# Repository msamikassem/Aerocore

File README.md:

# Aerocore — 3" Flight Controller

Aerocore is a flight controller for 3-inch FPV drones, built around an STM32F411 microcontroller and a BMI270 IMU. It handles IMU sensing, ESC motor control, USB configuration, and power regulation from a 4S LiPo on a single 4-layer board.

## What it does

- Runs an STM32F411CEU6 (Cortex-M4, 100MHz) as the main flight computer
- BMI270 6-axis IMU over SPI for gyro/accel
- USB-C mainly for serial communication with a PC
- Powers itself from a 4S LiPo, steps down to 5V (buck) and 3.3V (LDO) on board
- Drives 4 ESCs via PWM 
- UART header for an ELRS receiver
- Dedicated ST-Link header for programming/debugging
- 2 status LEDs + 2 power LEDS (5v and 3v)

## Key specs

| | |
|---|---|
| MCU | STM32F411CEU6, 100MHz Cortex-M4, QFN48 |
| IMU | Bosch BMI270, SPI |
| Input power | 4S LiPo (up to 60A absolute max draw, 15A per motor) |
| Onboard rails | 5V (LMR51430 buck), 3.3V (TLV75533 LDO) |
| USB | USB-C, USB2.0 full-speed |
| Board | 4 layers, 36×36mm, 1.6mm thick |
| Stackup | JLC04161H-7628 (1oz outer / 0.5oz inner copper) |
| Mounting holes | 4× M2.5, 26.5×26.5mm spacing|

## Repo layout

```
hardware/                           -> PCB files
    kicad/                          -> the actual schematic + PCB source files (final version)
    Component/      
        Data_sheets/                -> Data sheets of chosen components 
        My_FootPrints.pretty/       -> FootPrints not avaliable on KiCAD
        Schematics/                 -> Schematics not avaliable on KiCAD
        3D part/                    -> Components' 3D model
    archive/                        -> PCB V1
    manufacturing/                  -> files needed by PCB manufacturer
        bom/                        -> bill of material
        cpl/                        -> component placement
        DRC/                        -> KiCAD Error and warning reports
    
firmware/                           -> flight firmware
docs/
    design-log                      -> PCB design decisions and difficulties
    specs                           -> PCB specifications  
```

## Status

- [X] Schematic design
- [X] PCB layout
- [X] Ordered from JLCPCB
- [X] Board assembled and bring-up tested
- [ ] Firmware
- [ ] First flight

## Tools used

- KiCad 7 for schematic + PCB

## License

MIT — see [LICENSE](LICENSE). Feel free to use any of this for your own projects; if you spot a mistake I haven't caught yet, I'd genuinely like to know.

## Author

Mohammed Kassem — built as a personal project. [msamikassem@gmail.com/ linkedin.com/in/msamikassem]

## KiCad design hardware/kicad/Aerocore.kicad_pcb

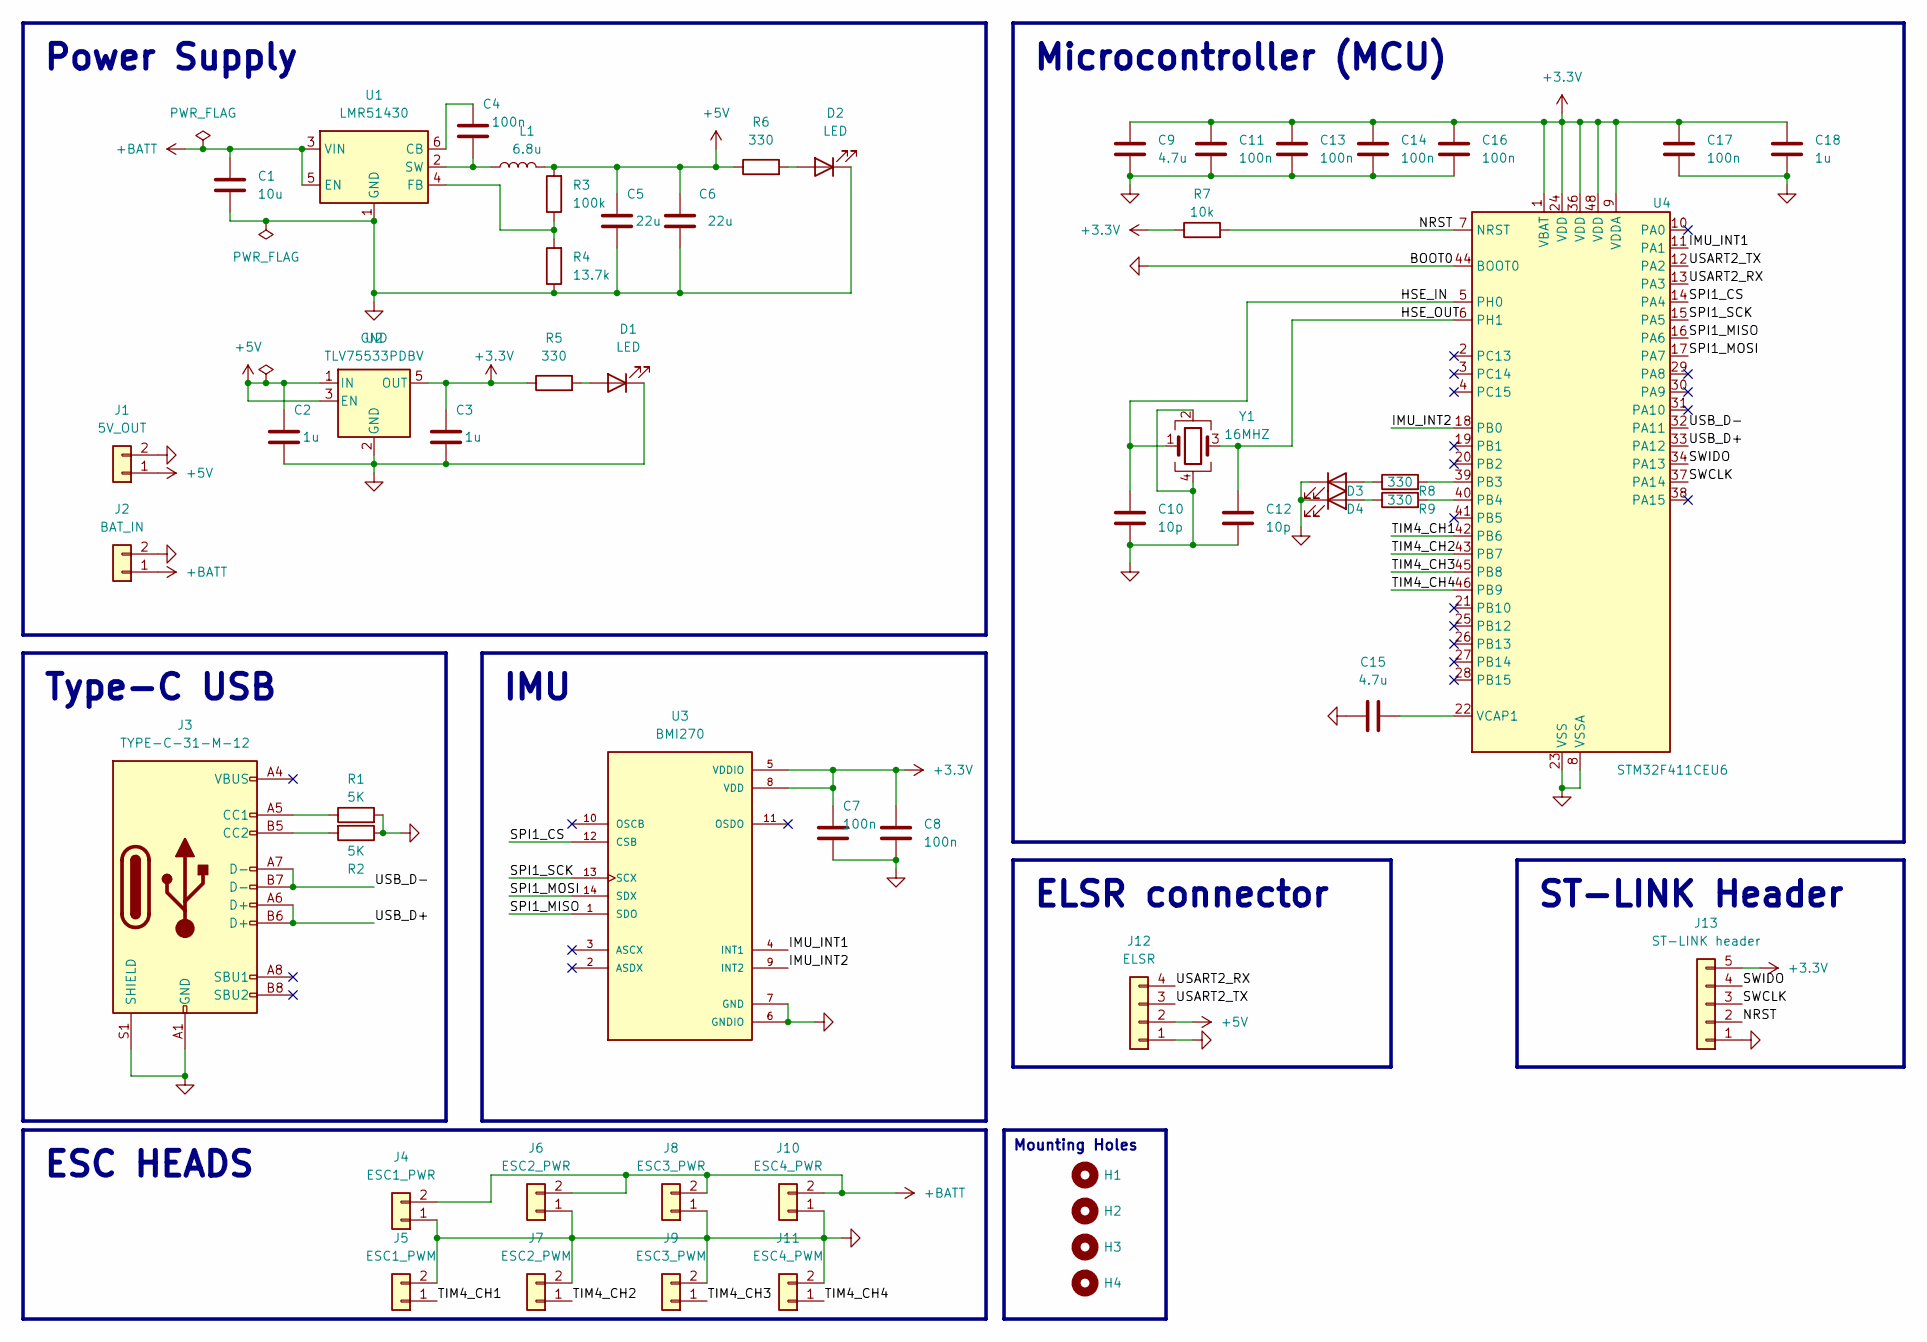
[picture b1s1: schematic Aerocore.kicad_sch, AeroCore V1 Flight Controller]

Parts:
C1: 10u; C_0603_1608Metric
C2, C3, C18: 1u; C_0603_1608Metric
C4, C7, C8, C11, C13, C14, C16, C17: 100n; C_0402_1005Metric
C5, C6: 22u; C_1206_3216Metric
C9, C15: 4.7u; C_0603_1608Metric
C10, C12: 10p; C_0603_1608Metric
D1, D2, D3, D4: LED; LED_0603_1608Metric
H1, H2, H3, H4: MountingHole_2.7mm
J1: 5V_OUT; Power_Pad_1.5x1.5mm
J2: BAT_IN; Power_Pad_1.5x1.5mm
J3: TYPE-C-31-M-12; USB_C_Receptacle_G-Switch_GT-USB-7010ASV
J4: ESC1_PWR; Power_Pad_2.5x3.5mm
J5: ESC1_PWM; Power_Pad_1.5x1.5mm
J6: ESC2_PWR; Power_Pad_2.5x3.5mm
J7: ESC2_PWM; Power_Pad_1.5x1.5mm
J8: ESC3_PWR; Power_Pad_2.5x3.5mm
J9: ESC3_PWM; Power_Pad_1.5x1.5mm
J10: ESC4_PWR; Power_Pad_2.5x3.5mm
J11: ESC4_PWM; Power_Pad_1.5x1.5mm
J12: ELSR; Power_Pad_4_1.5x1.5mm
J13: ST-LINK header; Solder_Pad_5_1.5x1.5mm
L1: 6.8u; L_Sunlord_MWSA0603S
R1, R2: 5K; R_0603_1608Metric
R3: 100k; R_0603_1608Metric
R4: 13.7k; R_0603_1608Metric
R5, R6, R8, R9: 330; R_0603_1608Metric
R7: 10k; R_0603_1608Metric
U1: LMR51430; SOT-23-6
U2: TLV75533PDBV; SOT-23-5
U3: BMI270; XDCR_BMI270
U4: STM32F411CEU6; QFN-48-1EP_7x7mm_P0.5mm_EP5.6x5.6mm
Y1: 16MHZ; Crystal_SMD_3225-4Pin_3.2x2.5mm

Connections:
+3.3V: C3.1, C7.1, C8.1, C9.1, C11.1, C13.1, C14.1, C16.1, C17.1, C18.1, J13.5, R5.1, R7.1, U2.5 (OUT), U3.5 (VDDIO), U3.8 (VDD), U4.1 (VBAT), U4.9 (VDDA), U4.24 (VDD), U4.36 (VDD), U4.48 (VDD)
+5V: C2.1, C5.1, C6.1, J1.1, J12.2, L1.2, R3.2, R6.1, U2.1 (IN), U2.3 (EN)
+BATT: C1.1, J2.1, J4.2, J6.2, J8.2, J10.2, U1.3 (VIN), U1.5 (EN)
/HSE_IN: C10.1, U4.5 (PH0), Y1.1
/HSE_OUT: C12.1, U4.6 (PH1), Y1.3
/IMU_INT1: U3.4 (INT1), U4.11 (PA1)
/IMU_INT2: U3.9 (INT2), U4.18 (PB0)
/NRST: J13.2, R7.2, U4.7 (NRST)
/SPI1_CS: U3.12 (CSB), U4.14 (PA4)
/SPI1_MISO: U3.1 (SDO), U4.16 (PA6)
/SPI1_MOSI: U3.14 (SDX), U4.17 (PA7)
/SPI1_SCK: U3.13 (SCX), U4.15 (PA5)
/SWCLK: J13.3, U4.37 (PA14)
/SWIDO: J13.4, U4.34 (PA13)
/TIM4_CH1: J5.1, U4.42 (PB6)
/TIM4_CH2: J7.1, U4.43 (PB7)
/TIM4_CH3: J9.1, U4.45 (PB8)
/TIM4_CH4: J11.1, U4.46 (PB9)
/USART2_RX: J12.4, U4.13 (PA3)
/USART2_TX: J12.3, U4.12 (PA2)
/USB_D+: J3.A6 (D+), J3.B6 (D+), U4.33 (PA12)
/USB_D-: J3.A7 (D-), J3.B7 (D-), U4.32 (PA11)
GND: C1.2, C2.2, C3.2, C5.2, C6.2, C7.2, C8.2, C9.2, C10.2, C11.2, C12.2, C13.2, C14.2, C15.1, C16.2, C17.2, C18.2, D1.1 (K), D2.1 (K), D3.1 (K), D4.1 (K), J1.2, J2.2, J3.A1 (GND), J3.A12 (GND), J3.B1 (GND), J3.B12 (GND), J3.S1 (SHIELD), J4.1, J5.2, J6.1, J7.2, J8.1, J9.2, J10.1, J11.2, J12.1, J13.1, R1.2, R2.1, R4.1, U1.1 (GND), U2.2 (GND), U3.6 (GNDIO), U3.7 (GND), U4.8 (VSSA), U4.23 (VSS), U4.35 (VSS), U4.44 (BOOT0), U4.47 (VSS), U4.49 (VSS), Y1.2, Y1.4
unnamed: D1.2 (A), R5.2
unnamed: D2.2 (A), R6.2
unnamed: D3.2 (A), R8.1
unnamed: D4.2 (A), R9.1
unnamed: J3.A5 (CC1), R1.1
unnamed: J3.B5 (CC2), R2.2
unnamed: C4.2, U1.6 (CB)
unnamed: R3.1, R4.2, U1.4 (FB)
unnamed: C4.1, L1.1, U1.2 (SW)
unnamed: R8.2, U4.39 (PB3)
unnamed: R9.2, U4.40 (PB4)
unnamed: C15.2, U4.22 (VCAP1)

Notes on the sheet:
Power Supply
ST-LINK Header
ESC HEADS
Mounting Holes
ELSR connector
IMU
Microcontroller (MCU)
Type-C USB

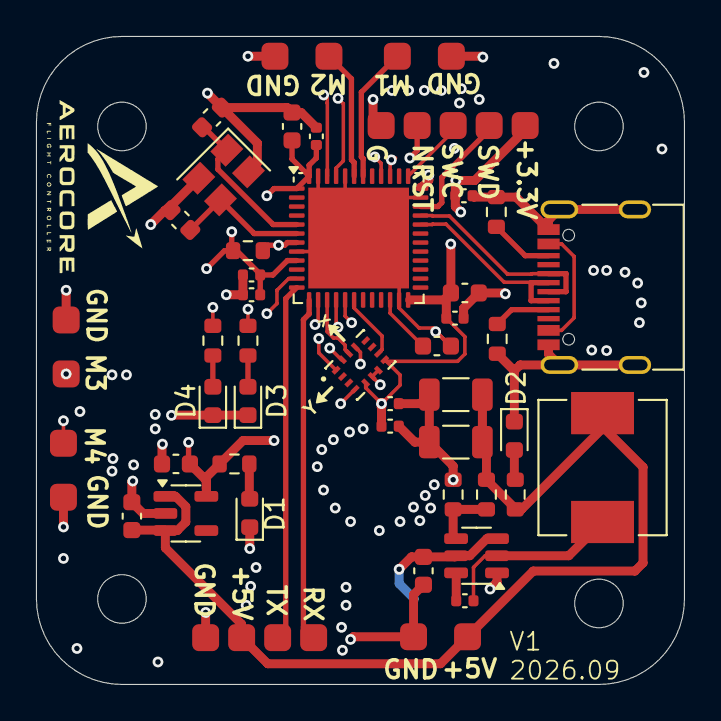
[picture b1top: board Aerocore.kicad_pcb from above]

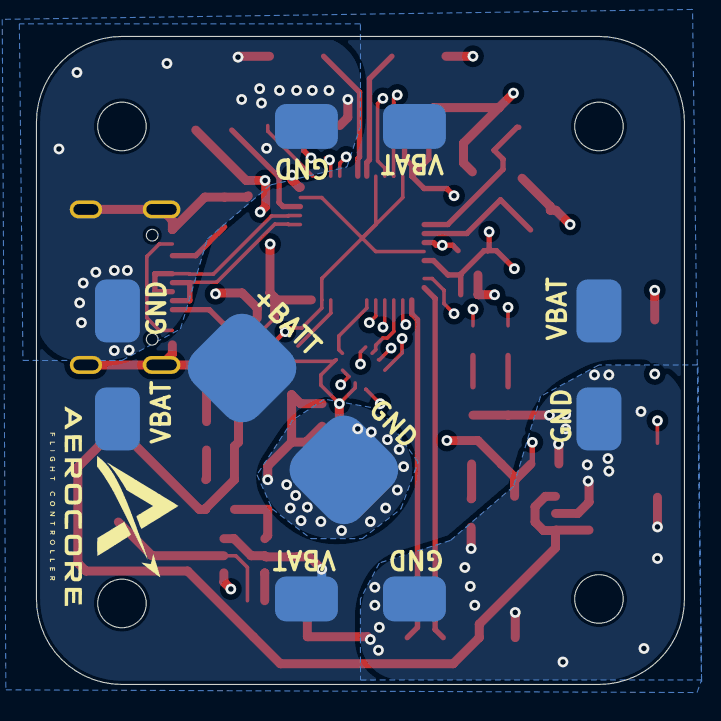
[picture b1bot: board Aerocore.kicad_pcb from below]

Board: 4 copper layers, 36.0 x 36.0 mm, 54 parts (5 on the bottom side), 35 nets.

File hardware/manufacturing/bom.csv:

"Comment","Designator","Footprint","LCSC Part #"
"10u","C1","Capacitor_SMD:C_0603_1608Metric","C1713"
"1u","C2, C3, C18","Capacitor_SMD:C_0603_1608Metric","C1592"
"100n","C4, C7, C8, C11, C13, C14, C16, C17","Capacitor_SMD:C_0402_1005Metric","C1525"
"22u","C5, C6","Capacitor_SMD:C_1206_3216Metric","C1859"
"4.7u","C9, C15","Capacitor_SMD:C_0603_1608Metric","C1705"
"10p","C10, C12","Capacitor_SMD:C_0603_1608Metric","C1634"
"LED","D1, D2, D3, D4","LED_SMD:LED_0603_1608Metric","C2288"
"TYPE-C-31-M-12","J3","Connector_USB:USB_C_Receptacle_G-Switch_GT-USB-7010ASV","C165948"
"6.8u","L1","Inductor_SMD:L_Sunlord_MWSA0603S","C408449"
"5K","R1, R2","Resistor_SMD:R_0603_1608Metric","C166926"
"100k","R3","Resistor_SMD:R_0603_1608Metric","C14675"
"13.7k","R4","Resistor_SMD:R_0603_1608Metric","C22793"
"330","R5, R6, R8, R9","Resistor_SMD:R_0603_1608Metric","C49254170"
"10k","R7","Resistor_SMD:R_0603_1608Metric","C25804"
"LMR51430","U1","Package_TO_SOT_SMD:SOT-23-6","C5185863"
"TLV75533PDBV","U2","Package_TO_SOT_SMD:SOT-23-5","C404027"
"BMI270","U3","Custom:XDCR_BMI270","C2836813"
"STM32F411CEU6","U4","Package_DFN_QFN:QFN-48-1EP_7x7mm_P0.5mm_EP5.6x5.6mm","C60420"
"16MHZ","Y1","Crystal:Crystal_SMD_3225-4Pin_3.2x2.5mm","C112972"

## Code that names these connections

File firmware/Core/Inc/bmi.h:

/******************************************************************************
 * Copyright (C) 2026 by Mohammed Kassem
 *
 * This software is provided for educational purposes.
 *
 *****************************************************************************/
/**
 * @file bmi.h
 * @brief BMI270 IMU driver for the STM32F411
 *
 * This file contains the function declarations for the BMI270
 * accelerometer and gyroscope. The sensor is connected to SPI1
 * (PA4 = CS, PA5 = SCK, PA6 = MISO, PA7 = MOSI). The data-ready
 * interrupt pin INT1 is connected to PA1 (EXTI line 1).
 *
 * Accelerometer: +-4g (8192 LSB/g), output rate 1600 Hz
 * Gyroscope: +-250 dps (131.2 LSB/dps), output rate 1600 Hz
 *
 * Every time a new sample is ready, the BMI270 raises INT1. The
 * interrupt handler reads the sensor, stores the data and the number
 * of clock cycles since the previous sample, and sets imu_ready.
 *
 * @author Mohammed Kassem
 * @date 04/10/2026
 *
 */

#ifndef BMI_H
#define BMI_H

#include <stdint.h>

/** Size of the BMI270 configuration file in bytes */
#define BMI270_CONFIG_SIZE  8192U

/** BMI270 configuration file (defined in bmi_config.c) */
extern const uint8_t bmi270_config_file[BMI270_CONFIG_SIZE];

/** Set to 1 by the interrupt when new data is ready. Clear it after use */
extern volatile uint8_t  imu_ready;

/** CPU clock cycles (DWT->CYCCNT) since the previous interrupt */
extern volatile uint32_t imu_cycles;

/** Latest gyroscope data p, q, r in degrees per second */
extern volatile float    imu_gyro[3];

/** Latest accelerometer data ax, ay, az in g */
extern volatile float    imu_accel[3];

/**
 * @brief Sets up the SPI pins and SPI1, then reads the BMI270 CHIP_ID
 *
 * This function configures PA4-PA7, initializes SPI1 and does a
 * dummy read to switch the BMI270 from I2C to SPI mode. It then
 * reads the CHIP_ID register.
 *
 * @return CHIP_ID of the sensor (0x24 for the BMI270)
 */
uint8_t verify_bmi(void);

/**
 * @brief Initializes the BMI270
 *
 * This function checks the CHIP_ID, uploads the configuration file,
 * configures the accelerometer and gyroscope, turns them on and
 * sets up the data-ready interrupt. It must be called once at
 * startup before reading any data. The DWT cycle counter must be
 * started before calling it.
 *
 * @return 1 if the initialization worked, 0 if it failed
 */
uint8_t bmi_init(void);

/**
 * @brief Sets up the data-ready interrupt
 *
 * This function configures the BMI270 INT1 pin (active high,
 * push-pull, data-ready) and sets up PA1 as a rising edge external
 * interrupt (EXTI1). It is called by bmi_init().
 */
void bmi_int_init(void);

/**
 * @brief Interrupt handler for EXTI line 1 (BMI270 INT1)
 *
 * This function runs every time a new sample is ready. It stores
 * the clock cycles since the last interrupt in imu_cycles and
 * resets the cycle counter. It then reads the accelerometer and
 * gyroscope into imu_accel and imu_gyro and sets imu_ready to 1.
 */
void EXTI1_IRQHandler(void);

/**
 * @brief Reads one BMI270 register
 *
 * @param reg Register address
 * @return Value of the register
 */
uint8_t bmi_read_reg(uint8_t reg);

/**
 * @brief Writes one BMI270 register
 *
 * @param reg Register address
 * @param value Value to write
 */
void bmi_write_reg(uint8_t reg, uint8_t value);

/**
 * @brief Reads multiple BMI270 registers in one transaction
 *
 * The dummy byte that the BMI270 sends first during an SPI read
 * is discarded.
 *
 * @param reg Address of the first register
 * @param data Buffer to store the data
 * @param len Number of bytes to read
 */
void bmi_read_burst(uint8_t reg, uint8_t *data, uint32_t len);

/**
 * @brief Uploads the configuration file to the BMI270
 *
 * The BMI270 needs this file after every power up or reset,
 * otherwise the sensor data stays at zero.
 */
void bmi_load_config(void);

/**
 * @brief Reads the raw accelerometer data
 *
 * @param x Raw X value (8192 LSB/g)
 * @param y Raw Y value (8192 LSB/g)
 * @param z Raw Z value (8192 LSB/g)
 */
void bmi_read_accel(int16_t *x, int16_t *y, int16_t *z);

/**
 * @brief Reads the raw gyroscope data
 *
 * @param x Raw X value (131.2 LSB/dps)
 * @param y Raw Y value (131.2 LSB/dps)
 * @param z Raw Z value (131.2 LSB/dps)
 */
void bmi_read_gyro(int16_t *x, int16_t *y, int16_t *z);

/**
 * @brief Reads the accelerometer data in g
 *
 * @param x X acceleration in g
 * @param y Y acceleration in g
 * @param z Z acceleration in g
 */
void bmi_read_accel_g(float *x, float *y, float *z);

/**
 * @brief Reads the gyroscope data in degrees per second
 *
 * @param x X angular rate in dps
 * @param y Y angular rate in dps
 * @param z Z angular rate in dps
 */
void bmi_read_gyro_dps(float *x, float *y, float *z);

#endif /* BMI_H */

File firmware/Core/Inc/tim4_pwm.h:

/****************************************************************************
 * Copyright (C) 2026 by Mohammed Kassem
 *
 * This software is provided for educational purposes.
 *
 ****************************************************************************/
/**
 * @file tim4_pwm.h
 * @brief TIM4 PWM configuration for the STM32F411
 *
 * This file contains the function declarations for configuring
 * TIM4 PWM outputs on PB6, PB7, PB8 and PB9 for controlling
 * four ESCs.
 *
 * @author Mohammed Kassem
 * @date 10/10/2026
 *
 */

#ifndef TIM4_PWM_H
#define TIM4_PWM_H

#include <stdint.h>

/**
 * @brief Configures all four TIM4 PWM channels
 *
 * Configures PB6, PB7, PB8 and PB9 as alternate function outputs.
 * Sets the PWM frequency to 50 Hz and initializes all channels
 * to a 1000 us pulse width.
 */
void tim4_pwm(void);

/**
 * @brief Converts an input value to a PWM value
 *
 * @param input Value between 0.0 and 1.0
 * @return PWM value between 1000 and 2000
 */
uint32_t input_to_pwm(float input);

/**
 * @brief Changes the PWM value of a selected channel
 *
 * @param channel TIM4 channel (1-4)
 * @param value Input between 0.0 and 1.0
 */
void change_pwm(uint8_t channel, float value);

#endif /* TIM4_PWM_H */

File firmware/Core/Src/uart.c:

/******************************************************************************
 * Copyright (C) 2026 by Mohammed Kassem
 *
 * This software is provided for educational purposes.
 *
 *****************************************************************************/
/**
 * @file uart.c
 * @brief USART2 driver for the radio receiver on the STM32F411
 *
 * This file implements a simple polling driver for USART2. The radio
 * receiver is connected to PA2 (TX) and PA3 (RX), both using alternate
 * function AF7. The USART runs at 420000 baud with 8 data bits, no parity
 * and 1 stop bit. The baud rate register is calculated from the 16 MHz
 * clock the USART runs from at startup (HSI).
 *
 * @author Mohammed Kassem
 * @date 10/09/2026
 *
 */

#include "stm32f4xx.h"
#include "uart.h"
#include <stdint.h>
#include "crsf.h"        // add this


// Clock and baud rate
#define SYS_CLK     (48000000U)    // APB1 clock after clock_96MHz()
#define USART_CLK   (SYS_CLK)
#define BAUDRATE    (420000U)

// Pins (GPIOA)
#define PIN_TX      2U      // PA2 = USART2_TX
#define PIN_RX      3U      // PA3 = USART2_RX
#define AF_USART2   7U      // alternate function 7 (AF07)

volatile uint8_t  rc_ready = 0;
volatile uint32_t rc_last_tick = 0;     // time (ms) of the last decoded RC packet
volatile uint8_t  rc_seen = 0;          // 1 after the first packet

void UART2_init(void)
{
    // Provide CLK to GPIOA (AHB1) and USART2 (APB1)
    RCC->AHB1ENR |= RCC_AHB1ENR_GPIOAEN;
    RCC->APB1ENR |= RCC_APB1ENR_USART2EN;

    // Set PA2 (TX) and PA3 (RX) to alternate function mode (10)
    GPIOA->MODER &= ~(3U << (PIN_TX * 2U));
    GPIOA->MODER |=  (2U << (PIN_TX * 2U));
    GPIOA->MODER &= ~(3U << (PIN_RX * 2U));
    GPIOA->MODER |=  (2U << (PIN_RX * 2U));

    // Select AF7 (USART2) on AFRL, 4 bits per pin
    GPIOA->AFR[0] &= ~(0xFU << (PIN_TX * 4U));
    GPIOA->AFR[0] |=  (AF_USART2 << (PIN_TX * 4U));
    GPIOA->AFR[0] &= ~(0xFU << (PIN_RX * 4U));
    GPIOA->AFR[0] |=  (AF_USART2 << (PIN_RX * 4U));

    // Baud rate = USART_CLK / BRR (rounded to the nearest integer)
    USART2->BRR = (uint16_t)((USART_CLK + BAUDRATE / 2U) / BAUDRATE);

    // Enable transmitter, receiver and the USART
    USART2->CR1 = USART_CR1_TE | USART_CR1_RE | USART_CR1_UE;

    USART2->CR1 |= USART_CR1_RXNEIE;       // interrupt when a byte is received
    NVIC_SetPriority(USART2_IRQn, 0);
    NVIC_EnableIRQ(USART2_IRQn);
}


uint8_t UART2_read(void)
{
    // Wait until a byte has been received (RXNE flag)
    while (!(USART2->SR & USART_SR_RXNE))
    {
    }

    // Reading DR also clears the RXNE flag
    return (uint8_t)USART2->DR;
}

void USART2_IRQHandler(void)
{
    if (USART2->SR & (USART_SR_RXNE | USART_SR_ORE))
    {
        uint8_t b = (uint8_t)USART2->DR;

        if (CRSF_process_byte(b))
        {
            rc_ready = 1;
            rc_last_tick = HAL_GetTick();
            rc_seen = 1;
        }
    }
}

void UART2_send(const uint8_t *data, uint8_t length)
{
    for (uint8_t i = 0; i < length; i++)
    {
        // Wait until USART can accept another byte
        while (!(USART2->SR & USART_SR_TXE))
        {
        }

        // Send the next byte
        USART2->DR = data[i];
    }

    // Wait until the final byte has finished transmitting
    while (!(USART2->SR & USART_SR_TC))
    {
    }
}
